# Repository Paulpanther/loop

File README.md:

```

                      ---------------------   LOOP   ---------------------

                      led earrings using nOOds [adafruit.com/product/5504]

                                                   =****+++++=.                     
                                            =#*******++++=======--..                
                                        ########*++++++++++=======--..              
                                    *@######*******+++++--....                      
                                 -@@#####**********==------....                     
                               @@######*********======------...                     
                             @@######********===========-                           
                           @@@@####********==========-                              
                         @@@@@@@@###*****=========-                                 
                        @@@@@@@########+++++====.                                   
                      *@@@@@@@#######*++++++++.                                     
                     @@@@@@@@#######++++++++.                                       
                    @@@@@@@########++++++++                                         
                   @@@@@@@#######++++++++.                                          
                  @@@@@@@#######++++++++                                            
                 @@@@@@@#######++++++++                         +==-=.-----    ..   
                @@@@@@@#######++++++++                           #*++++=====..----  
               =@@@@@@@######++++++++                             ##****+++++=--=== 
               @@@@@@@######*+++++++                              @######*****===== 
              @@@@@@@#######+++++++                               =@@@####*****=====
              @@@@@@@######+++++++                                =@@@####*****=====
             =@@@@@@######*++++++=                                =@@@@@##*****+++++
             @@@@@@@######+++++++                                 *@@@@@@@#####+++++
             @@@@@@#######++++++.                                 @@@@@@@@#####+++++
             @@@@@@######+++++++                                  @@@@@@@@#####++++-
            #@@@@@@######+++++++                                 @@@@@@@@@####+++++ 
            #@@@@@@######++++++                                 @@@@@@@@@#####+++++ 
            #@@@@@######*++++++                                @@@@@@@@@#####*++++  
             @@@@@######+++++++                               @@@@@@@@@######+++++  
             @@@@@######+++++++                              @@@@@@@@@######+++++   
             @@@@@@#####+++++++                            @@@@@####@######+++++    
             @@@@@@#####*++++++                          @##@@######***##*+++++     
              @@@@@######++++++                       -#####**####******++++++      
              @@##@######++++++=                 -=++++++++****++*****+===+++       
               @####*****+++++++                      .-==+===+++++*+======         
                @###******======.                         .-====++--=====.          
                 ####*****=======                          .-=- ..----=-            
                  ###******=======                               ..--               
                   ###******=======                                                 
                    ###******=======                                                
                      ##******====---                                               
                       ***+++++=-------                                             
                         ***+++++---....                                            
                           -**+++++..                                               
                               +======                                              
                                   .------
```

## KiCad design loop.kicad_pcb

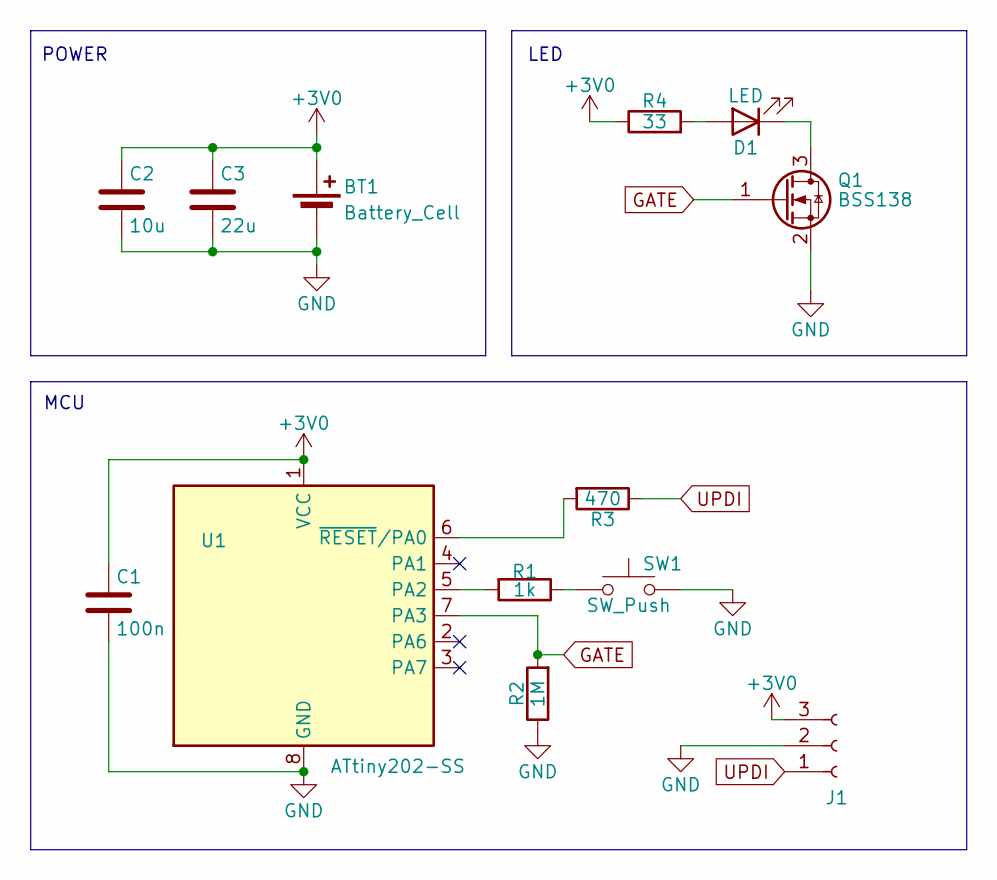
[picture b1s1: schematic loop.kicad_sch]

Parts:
BT1: Battery_Cell; BAT-SMD_MY-1220-03
C1: 100n; C_0805_2012Metric_Pad1.18x1.45mm_HandSolder
C2: 10u; C_0805_2012Metric_Pad1.18x1.45mm_HandSolder
C3: 22u; C_0805_2012Metric_Pad1.18x1.45mm_HandSolder
D1: LED; Led Nood
J1: Conn_01x03_Socket; PinSocket_1x03_P2.54mm_Vertical
Q1: BSS138; SOT-23
R1: 1k; R_0805_2012Metric_Pad1.20x1.40mm_HandSolder
R2: 1M; R_0805_2012Metric_Pad1.20x1.40mm_HandSolder
R3: 470; R_0805_2012Metric_Pad1.20x1.40mm_HandSolder
R4: 33; R_0805_2012Metric_Pad1.20x1.40mm_HandSolder
SW1: SW_Push; SW_SPST_TL3342
U1: ATtiny202-SS; SOIC-8_3.9x4.9mm_P1.27mm

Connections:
+3V0: BT1.1 (+), C1.1, C2.1, C3.1, J1.3, R4.1, U1.1 (VCC)
GATE: Q1.1 (G), R2.2, U1.7 (PA3)
GND: BT1.2 (-), C1.2, C2.2, C3.2, J1.2, Q1.2 (S), R2.1, SW1.2, U1.8 (GND)
unnamed: D1.2 (A), R4.2
unnamed: D1.1 (K), Q1.3 (D)
unnamed: R1.1, SW1.1
unnamed: R1.2, U1.5 (PA2)
unnamed: R3.2, U1.6 (~RESET/PA0)
UPDI: J1.1, R3.1

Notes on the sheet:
LED
POWER
MCU

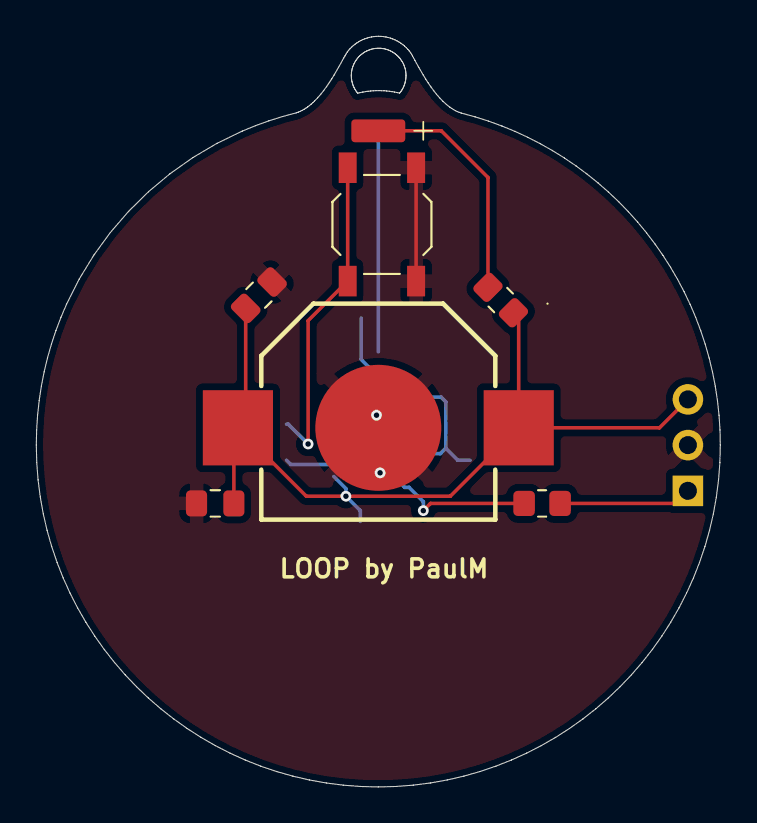
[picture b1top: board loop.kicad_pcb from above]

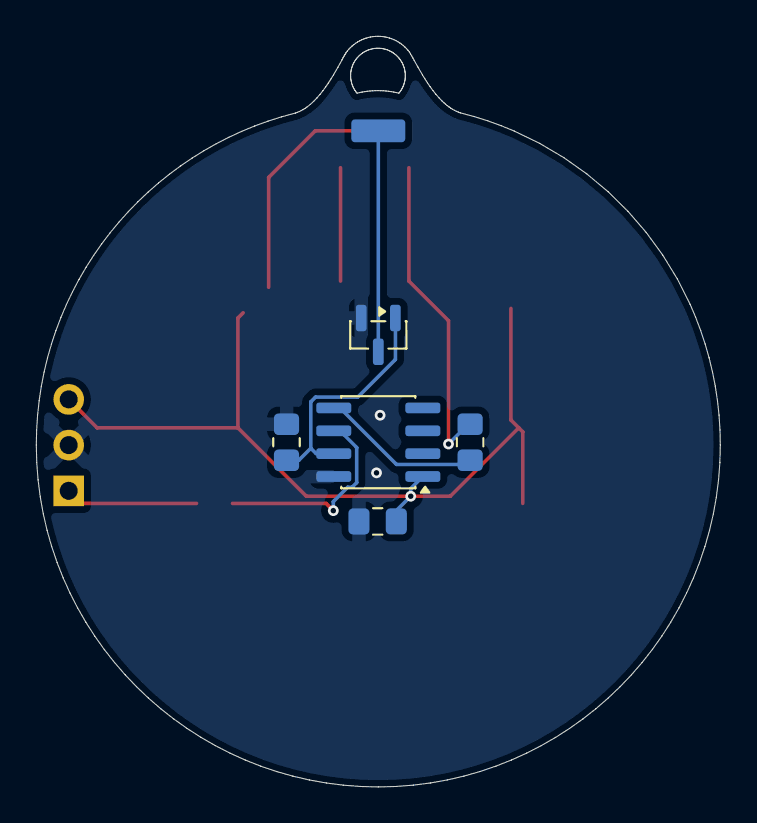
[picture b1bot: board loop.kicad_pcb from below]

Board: 2 copper layers, 38.0 x 41.7 mm, 13 parts (6 on the bottom side), 9 nets.
